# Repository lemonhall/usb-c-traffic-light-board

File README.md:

# USB-C 红绿灯控制板

这是一个用于替换原红绿灯小板的项目。目标是做一块新的 `57mm x 14mm` 电路板，通过 USB-C 供电，并让电脑通过 USB 串口控制红、黄、绿三颗灯。

## 目标

- 完全替换原来的小电路板。
- 使用 USB-C 供电。
- 通过 USB-C 连接电脑，由电脑控制三颗灯。
- 电脑端识别为虚拟串口，方便脚本控制。
- 尽量避免飞线，最终装配时只使用这一块新板。

## 当前机械假设

- 板长：`57mm`
- 板宽：`14mm`
- 当前板框已经按原板照片改成上下梯形端部和左右半圆避让槽。
- 三颗灯从上到下为：绿、黄、红；灯中心按从板底往上约 `50mm`、`28mm`、`7mm` 复核。
- 上螺丝孔直径 `2mm`，孔边离上端梯形窄边约 `1mm`。
- 下螺丝孔直径 `2mm`，孔中心离板顶约 `33mm`，位于板子左侧、靠近从下往上第二组避让槽。
- USB-C 目标位置对应原拨动开关穿出后壳的位置；原开关伸出背面约 `10mm`，开口宽度约 `10mm`。
- 注意：当前 KiCad 里 `USB_C_Receptacle_G-Switch_GT-USB-7025` 是 `right-angle` 占位封装，不是最终可下单的立式背出 USB-C；最终必须按实物型号替换封装和 3D 机械模型。

## 下一步顺序

1. 机械复核：量原板孔位、缺口、圆角、灯中心坐标、USB-C 后壳开口位置，把板框从当前矩形改成更贴原壳的形状。
2. USB-C 完整性复核：按最终采购的连接器封装，复核 `VBUS`、`GND`、`CC1`、`CC2`、`D+`、`D-`，确认正反插都能稳定供电和通信。
3. 生成生产文件：用 KiCad CLI 导出 Gerber 和钻孔文件，再用 Gerber 预览检查铜层、板框、孔、阻焊和丝印。
4. 小批打样前审查：逐项核对 BOM、封装方向、LED 极性、USB-C 型号、CH552G 供电和下载方式。

当前建议先做第 1 步和第 2 步。它们决定这块板能不能真的塞回外壳，以及插上电脑后能不能稳定识别。

## 电气方案

- 主控：沁恒 `CH552G`，小封装、带原生 USB。
- USB-C：
  - 电脑 USB-C 默认 `VBUS` 提供 `5V`。
  - 本板只作为普通受电设备，不做 USB PD 高压协商。
  - `D+ / D-` 接到主控 USB 引脚。
  - `CC1 / CC2` 各接一个 `5.1k` 下拉电阻到地，只做受电设备。
- 三颗灯：
  - 每颗灯单独串限流电阻。
  - 每颗灯由一个主控 GPIO 控制。
  - 固件可用 PWM 分别控制三颗灯亮度，也可以控制任意组合同时亮、闪烁或呼吸。
  - 第一版按低亮度指示灯设计，目标电流约 `2-5mA`。
- 调试：
  - 预留 `5V`、`GND`、`D+`、`D-`、复位、三路灯控制测试焊盘。

## 串口协议草案

电脑通过虚拟串口发送一行文本命令：

```text
R 1
R 0
Y 1
Y 0
G 1
G 0
A 0
A 1
S 1 0 1
?
```

返回示例：

```text
OK
ERR 1
S R=1 Y=0 G=1
```

## 文件说明

- `docs/hardware/requirements.md`：需求和边界。
- `docs/hardware/bom.md`：第一版物料清单。
- `docs/hardware/pinout.md`：引脚和网络分配。
- `docs/hardware/mechanical-measurement-guide.md`：原板外轮廓和孔位测量指南。
- `docs/hardware/serial-protocol.md`：电脑控制协议。
- `docs/hardware/schematic.md`：完整原理图连接说明。
- `docs/hardware/schematic.svg`：可直接打开查看的完整原理图。
- `docs/hardware/pcb-layout.svg`：第一版 PCB 顶层布局草案。
- `references/original-board-photo.md`：原板照片观察记录。
- `kicad/`：KiCad 工程骨架和第一版板框。
- `firmware/README.md`：固件设计说明。
- `pc-control/traffic_light.py`：电脑端串口控制小脚本。

## 已查资料

- CH552G 是带 USB 的 8 位单片机：https://www.alldatasheet.com/datasheet-pdf/pdf/1147065/WCH/CH552G.html
- LCSC 页面显示 CH552G 常见封装为 SOP-16：https://www.lcsc.com/product-detail/Microcontrollers-MCU-MPU-SOC_WCH-Jiangsu-Qin-Heng-CH552G_C111292.html
- CH552G 资料中包含 USB Type-C CC 控制相关内容：https://www.alldatasheet.net/html-pdf/1147065/WCH/CH552G/2781/41/CH552G.html

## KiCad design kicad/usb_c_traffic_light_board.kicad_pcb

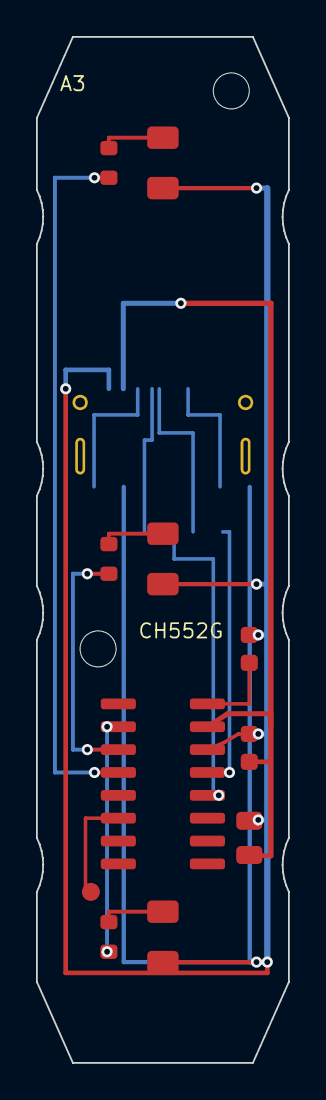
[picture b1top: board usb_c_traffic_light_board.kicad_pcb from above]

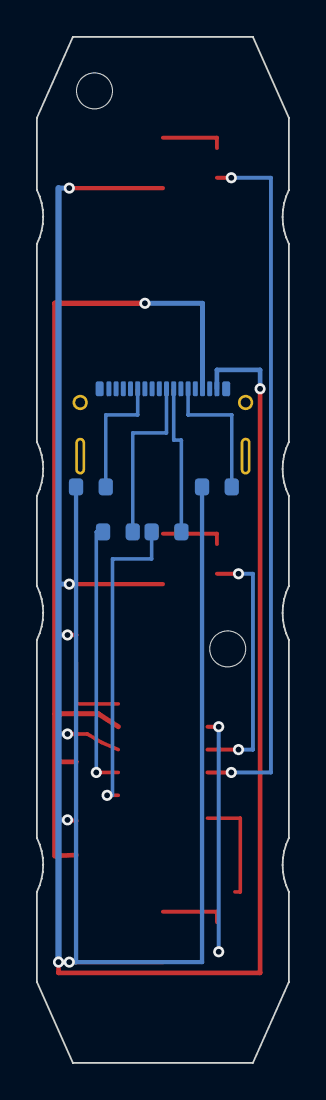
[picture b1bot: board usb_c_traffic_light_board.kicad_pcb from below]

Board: 2 copper layers, 14.0 x 57.0 mm, 18 parts (5 on the bottom side), 16 nets.

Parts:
C1: 10uF; C_0805_2012Metric
C2, C3: 100nF; C_0603_1608Metric
D1: 绿灯; LED_1206_3216Metric
D2: 橙灯; LED_1206_3216Metric
D3: 红灯; LED_1206_3216Metric
H1: 上螺丝孔; MountingHole_2mm
H2: 下螺丝孔; MountingHole_2mm
J1: 背面USB-C; USB_C_Receptacle_G-Switch_GT-USB-7025
R1, R2, R3: 1k; R_0603_1608Metric
R4, R5: 22R; R_0603_1608Metric
R6, R7: 5.1k; R_0603_1608Metric
TP1: RST; TestPoint_Pad_D1.0mm
U1: CH552G; SOIC-16_3.9x9.9mm_P1.27mm

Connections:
5V: C1.1, C2.1, J1.A4, U1.15
CC1: J1.A5, R6.1
CC2: J1.B5, R7.1
GND: C1.2, C2.2, C3.2, D1.1, D2.1, D3.1, J1.A1, R6.2, R7.2, U1.14
LED_G: R3.1, U1.4
LED_G_A: D1.2, R3.2
LED_R: R1.1, U1.2
LED_R_A: D3.2, R1.2
LED_Y: R2.1, U1.3
LED_Y_A: D2.2, R2.2
RST: TP1.1, U1.6
USB_D+: R4.2, U1.12
USB_D+_CONN: J1.A6, R4.1
USB_D-: R5.2, U1.13
USB_D-_CONN: J1.A7, R5.1
V33: C3.1, U1.16

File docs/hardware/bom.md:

# 第一版物料清单

| 位号 | 数量 | 器件 | 封装 | 说明 |
| --- | ---: | --- | --- | --- |
| J1 | 1 | USB-C 母座 | 只接 USB2.0 的贴片座 | 等确认外壳后选择沉板或普通贴片 |
| U1 | 1 | 沁恒 CH552G | SOP-16 | 带原生 USB 的单片机 |
| D1 | 1 | 绿灯 LED | 0805 或 1206 | 按外壳透光孔选择尺寸 |
| D2 | 1 | 黄灯 LED | 0805 或 1206 | 按外壳透光孔选择尺寸 |
| D3 | 1 | 红灯 LED | 0805 或 1206 | 按外壳透光孔选择尺寸 |
| R1 | 1 | 绿灯限流电阻 | 0603 或 0805 | 第一版从 `1k` 起步 |
| R2 | 1 | 黄灯限流电阻 | 0603 或 0805 | 第一版从 `1k` 起步 |
| R3 | 1 | 红灯限流电阻 | 0603 或 0805 | 第一版从 `1k` 起步 |
| R4 | 1 | USB D+ 串联电阻 | 0603 | 第一版按 `22Ω` 预留 |
| R5 | 1 | USB D- 串联电阻 | 0603 | 第一版按 `22Ω` 预留 |
| R6 | 1 | CC1 下拉电阻 | 0603 | `5.1k` 到地 |
| R7 | 1 | CC2 下拉电阻 | 0603 | `5.1k` 到地 |
| C1 | 1 | VBUS 输入电容 | 0805 | `4.7uF` 或 `10uF` |
| C2 | 1 | 主控去耦电容 | 0603 | `100nF`，靠近 U1 |
| C3 | 1 | USB/内部电源去耦 | 0603 | `100nF`，最终按参考设计确认 |
| TP1-TP8 | 8 | 测试焊盘 | 约 `1.0mm` 焊盘 | `5V`、地、USB、复位、三路灯 |

## 说明

- 第一版主控选 CH552G，是因为它小、便宜，并且自带 USB。
- LED 电阻先按室内指示灯亮度设计，实际亮度要结合外壳透光效果再调。
- 如果 USB-C 会频繁插拔，第二版建议加 USB 静电保护器件。
- 当前完整连接图见 `docs/hardware/schematic.svg`。

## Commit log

2026-05-25 第一版本
2026-05-25 提交红绿灯控制板阶段性设计
2026-05-25 完成红绿灯控制板布线
2026-05-25 完善机械轮廓和测量记录
2026-05-25 补充代理执行和布线流程
2026-05-25 记录机械复核和USB-C风险
2026-05-25 避位槽的深度不够，仍需修改
